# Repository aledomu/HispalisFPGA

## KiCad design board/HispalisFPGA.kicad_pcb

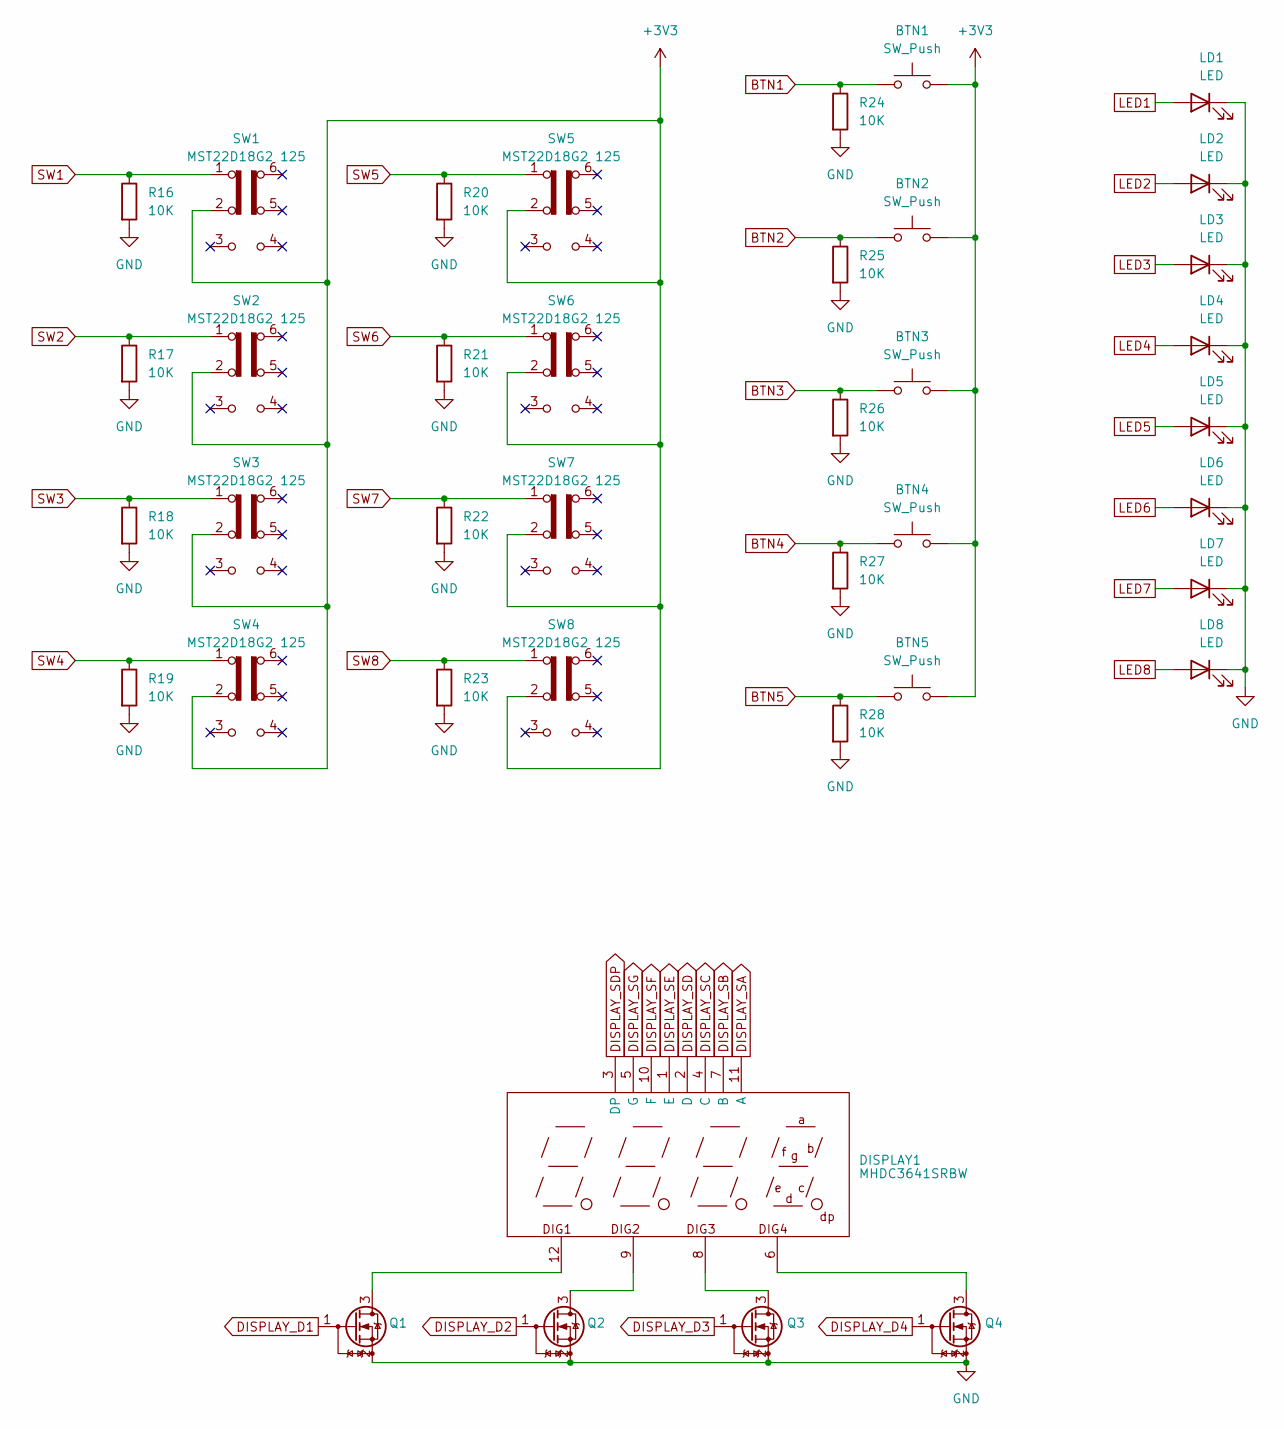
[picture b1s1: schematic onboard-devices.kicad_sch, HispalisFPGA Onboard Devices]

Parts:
BTN1, BTN2, BTN3, BTN4, BTN5: SW_Push; SW_PUSH_6mm; JLC Plugin,6x6mm
DISPLAY1: MHDC3641SRBW; LED-SEG-TH_12P-L30.0-W14.0-P2.54-LS10.2; Manufacturer Part MHDC3641SRBW; LCSC Part Name 0.36共阴四八红色数码管
LD1, LD2, LD3, LD4, LD5, LD6, LD7, LD8: LED; LED_0805_2012Metric; JLC 0805
Q1, Q2, Q3, Q4: DMG1012T; SOT-523; JLC SOT-523
R16, R17, R18, R19, R20, R21, R22, R23, R24, R25, R26, R27, R28: 10K; R_0402_1005Metric; JLC 0402
SW1, SW2, SW3, SW4, SW5, SW6, SW7, SW8: MST22D18G2 125; SW-SMD_MST22D18G2; JLC SMD

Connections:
+3V3: BTN1.2, BTN2.2, BTN3.2, BTN4.2, BTN5.2, SW1.2 (B), SW2.2 (B), SW3.2 (B), SW4.2 (B), SW5.2 (B), SW6.2 (B), SW7.2 (B), SW8.2 (B); also elsewhere on the board
BTN1: BTN1.1, R24.1; also elsewhere on the board
BTN2: BTN2.1, R25.1; also elsewhere on the board
BTN3: BTN3.1, R26.1; also elsewhere on the board
BTN4: BTN4.1, R27.1; also elsewhere on the board
BTN5: BTN5.1, R28.1; also elsewhere on the board
DISPLAY_D1: Q1.1 (G); also elsewhere on the board
DISPLAY_D2: Q2.1 (G); also elsewhere on the board
DISPLAY_D3: Q3.1 (G); also elsewhere on the board
DISPLAY_D4: Q4.1 (G); also elsewhere on the board
DISPLAY_SA: DISPLAY1.11 (A); also elsewhere on the board
DISPLAY_SB: DISPLAY1.7 (B); also elsewhere on the board
DISPLAY_SC: DISPLAY1.4 (C); also elsewhere on the board
DISPLAY_SD: DISPLAY1.2 (D); also elsewhere on the board
DISPLAY_SDP: DISPLAY1.3 (DP); also elsewhere on the board
DISPLAY_SE: DISPLAY1.1 (E); also elsewhere on the board
DISPLAY_SF: DISPLAY1.10 (F); also elsewhere on the board
DISPLAY_SG: DISPLAY1.5 (G); also elsewhere on the board
GND: LD1.1 (K), LD2.1 (K), LD3.1 (K), LD4.1 (K), LD5.1 (K), LD6.1 (K), LD7.1 (K), LD8.1 (K), Q1.2 (S), Q2.2 (S), Q3.2 (S), Q4.2 (S), R16.2, R17.2, R18.2, R19.2, R20.2, R21.2, R22.2, R23.2, R24.2, R25.2, R26.2, R27.2, R28.2; also elsewhere on the board
LED1: LD1.2 (A); also elsewhere on the board
LED2: LD2.2 (A); also elsewhere on the board
LED3: LD3.2 (A); also elsewhere on the board
LED4: LD4.2 (A); also elsewhere on the board
LED5: LD5.2 (A); also elsewhere on the board
LED6: LD6.2 (A); also elsewhere on the board
LED7: LD7.2 (A); also elsewhere on the board
LED8: LD8.2 (A); also elsewhere on the board
unnamed: DISPLAY1.12 (DIG1), Q1.3 (D)
unnamed: DISPLAY1.9 (DIG2), Q2.3 (D)
unnamed: DISPLAY1.8 (DIG3), Q3.3 (D)
unnamed: DISPLAY1.6 (DIG4), Q4.3 (D)
SW1: R16.1, SW1.1 (A); also elsewhere on the board
SW2: R17.1, SW2.1 (A); also elsewhere on the board
SW3: R18.1, SW3.1 (A); also elsewhere on the board
SW4: R19.1, SW4.1 (A); also elsewhere on the board
SW5: R20.1, SW5.1 (A); also elsewhere on the board
SW6: R21.1, SW6.1 (A); also elsewhere on the board
SW7: R22.1, SW7.1 (A); also elsewhere on the board
SW8: R23.1, SW8.1 (A); also elsewhere on the board

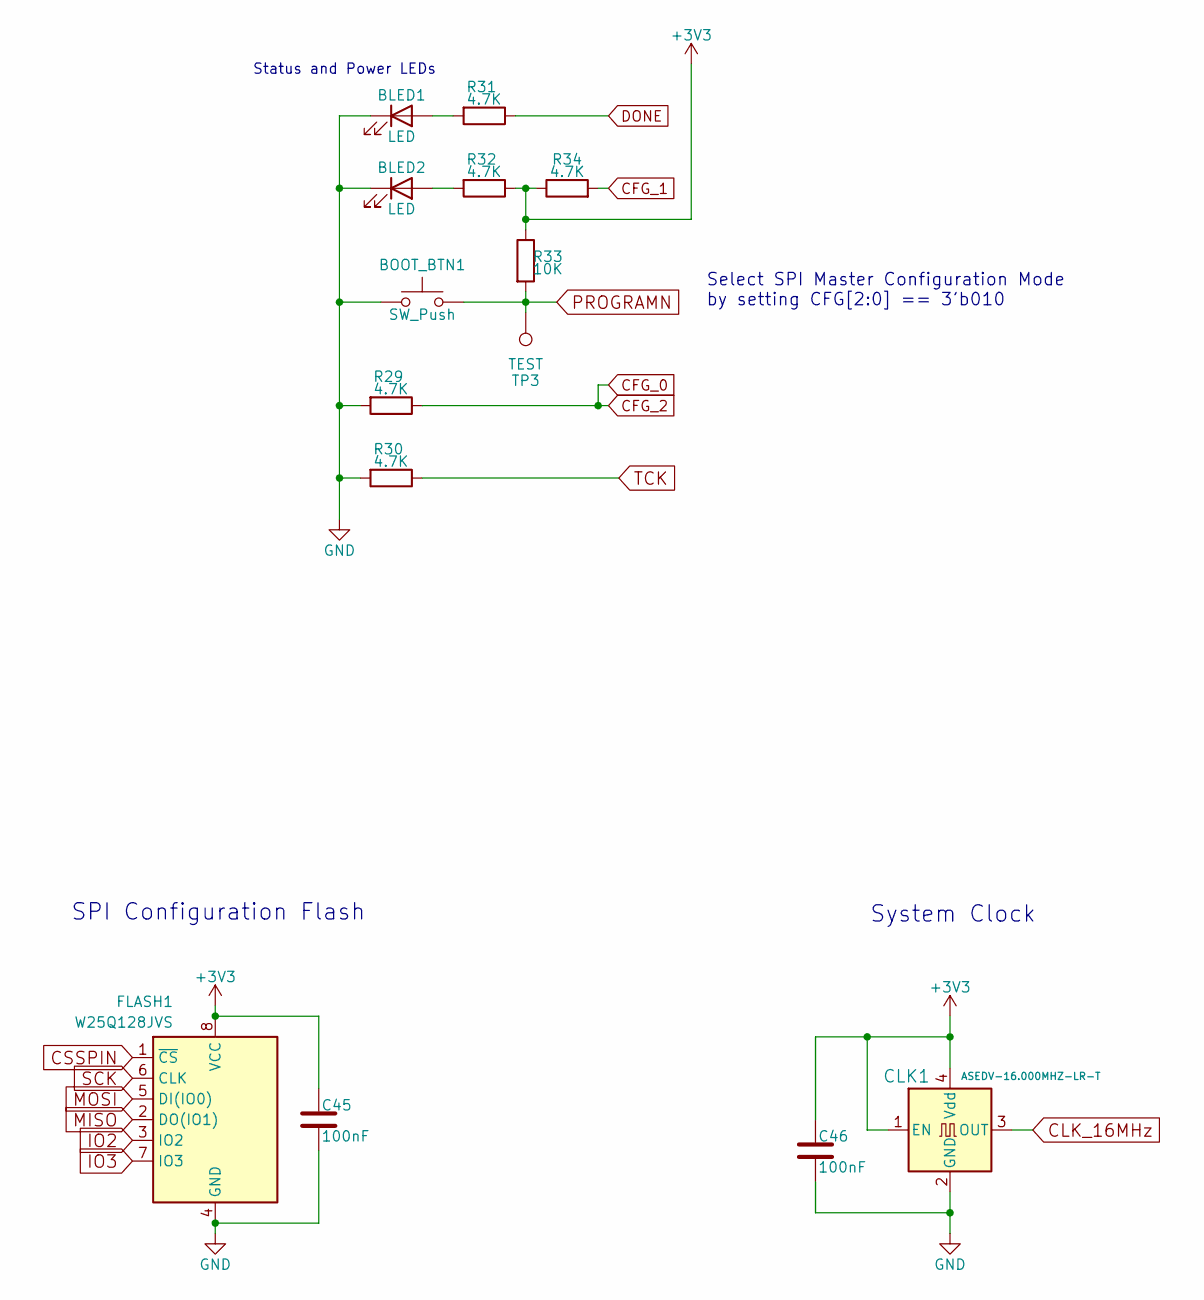
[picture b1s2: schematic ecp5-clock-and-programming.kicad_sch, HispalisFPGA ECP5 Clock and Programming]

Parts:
BLED1, BLED2: LED; LED_0603_1608Metric; JLC 0603
BOOT_BTN1: SW_Push; SW_PUSH_6mm; JLC Plugin,6x6mm
C45, C46: 100nF; C_0402_1005Metric; JLC 0402
CLK1: ASEDV-16.000MHZ-LR-T; Oscillator_SMD_Abracon_ASE-4Pin_3.2x2.5mm; JLC SMD3225-4P
FLASH1: W25Q128JVS; SOIC-8_5.23x5.23mm_P1.27mm; JLC SOIC-8-208mil
R29, R30, R31, R32, R34: 4.7K; R_0402_1005Metric; JLC 0402
R33: 10K; R_0402_1005Metric; JLC 0402
TP3: TEST; TestPoint_Pad_D1.0mm

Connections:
+3V3: C45.1, C46.1, CLK1.1 (EN), CLK1.4 (Vdd), FLASH1.8 (VCC), R32.1, R33.1, R34.1; also elsewhere on the board
CFG_0: R29.1; also elsewhere on the board
CFG_1: R34.2; also elsewhere on the board
CLK_16MHz: CLK1.3 (OUT); also elsewhere on the board
CSSPIN: FLASH1.1 (~CS); also elsewhere on the board
DONE: R31.1; also elsewhere on the board
GND: BLED1.1 (K), BLED2.1 (K), BOOT_BTN1.1, C45.2, C46.2, CLK1.2 (GND), FLASH1.4 (GND), R29.2, R30.2; also elsewhere on the board
IO2: FLASH1.3 (IO2); also elsewhere on the board
IO3: FLASH1.7 (IO3); also elsewhere on the board
MISO: FLASH1.2 (DO(IO1)); also elsewhere on the board
MOSI: FLASH1.5 (DI(IO0)); also elsewhere on the board
unnamed: BLED1.2 (A), R31.2
unnamed: BLED2.2 (A), R32.2
PROGRAMN: BOOT_BTN1.2, R33.2, TP3.1; also elsewhere on the board
SCK: FLASH1.6 (CLK); also elsewhere on the board
TCK: R30.1; also elsewhere on the board

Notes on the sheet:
System Clock
Status and Power LEDs
Select SPI Master Configuration Mode by setting CFG[2:0] == 3'b010
SPI Configuration Flash

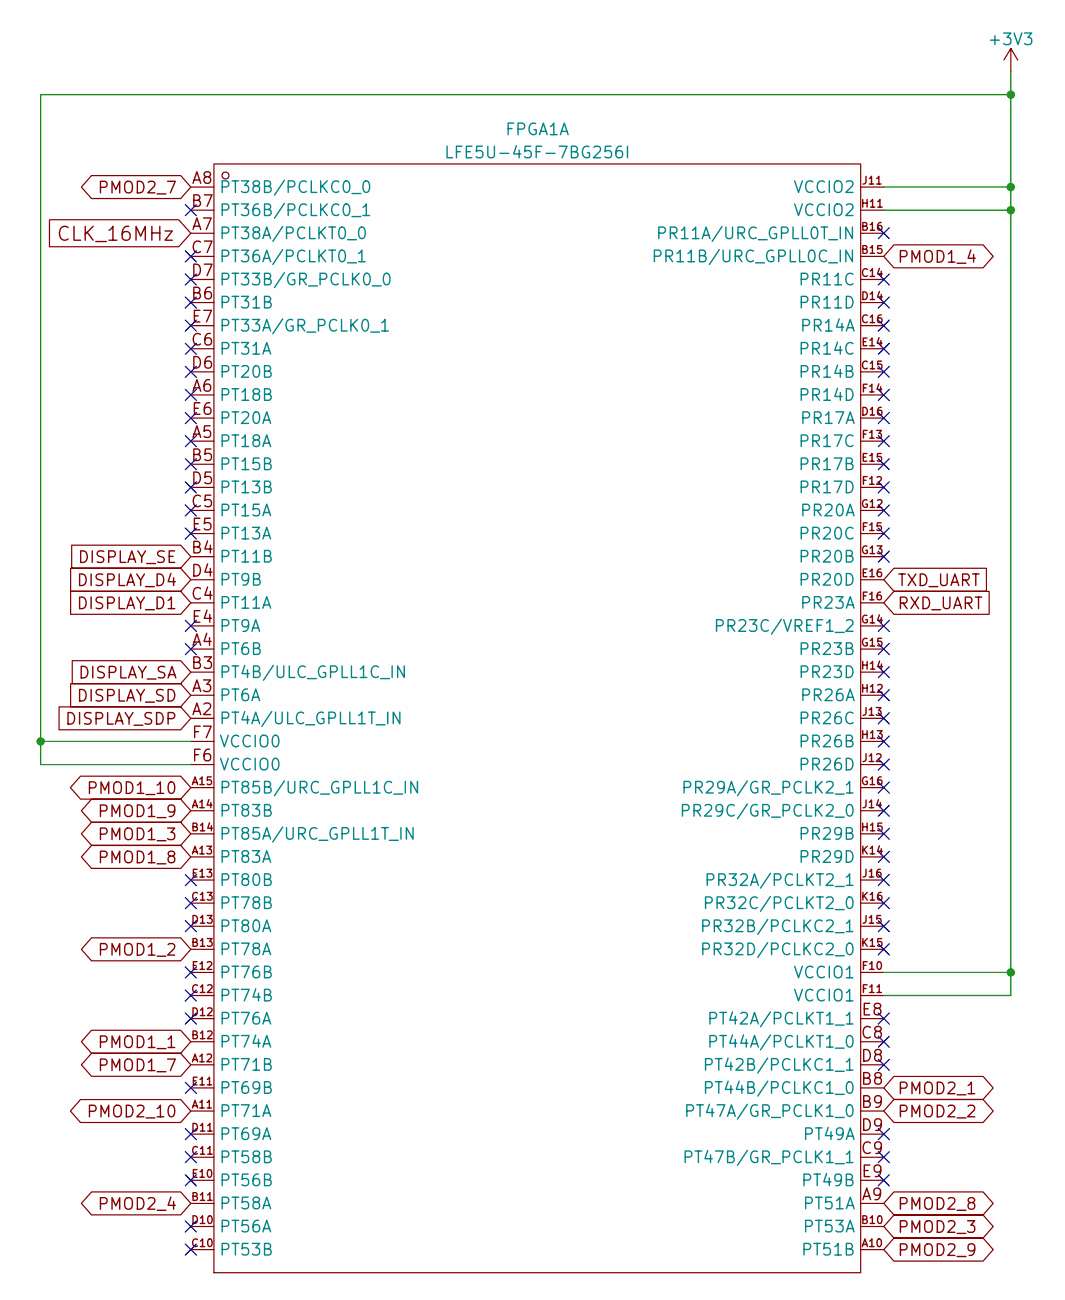
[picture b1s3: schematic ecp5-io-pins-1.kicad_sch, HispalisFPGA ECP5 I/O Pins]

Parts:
FPGA1: LFE5U-45F-7BG256I; CABGA-256_L14.0-W14.0-R16-C16-P0.80-TL; Manufacturer Part LFE5U-45F-7BG256I; LCSC Part Name LFE5U 45F 7BG256I

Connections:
+3V3: FPGA1.F6 (VCCIO0), FPGA1.F7 (VCCIO0), FPGA1.F10 (VCCIO1), FPGA1.F11 (VCCIO1), FPGA1.H11 (VCCIO2), FPGA1.J11 (VCCIO2); also elsewhere on the board
CLK_16MHz: FPGA1.A7 (PT38A/PCLKT0_0); also elsewhere on the board
DISPLAY_D1: FPGA1.C4 (PT11A); also elsewhere on the board
DISPLAY_D4: FPGA1.D4 (PT9B); also elsewhere on the board
DISPLAY_SA: FPGA1.B3 (PT4B/ULC_GPLL1C_IN); also elsewhere on the board
DISPLAY_SD: FPGA1.A3 (PT6A); also elsewhere on the board
DISPLAY_SDP: FPGA1.A2 (PT4A/ULC_GPLL1T_IN); also elsewhere on the board
DISPLAY_SE: FPGA1.B4 (PT11B); also elsewhere on the board
PMOD1_1: FPGA1.B12 (PT74A); also elsewhere on the board
PMOD1_2: FPGA1.B13 (PT78A); also elsewhere on the board
PMOD1_3: FPGA1.B14 (PT85A/URC_GPLL1T_IN); also elsewhere on the board
PMOD1_4: FPGA1.B15 (PR11B/URC_GPLL0C_IN); also elsewhere on the board
PMOD1_7: FPGA1.A12 (PT71B); also elsewhere on the board
PMOD1_8: FPGA1.A13 (PT83A); also elsewhere on the board
PMOD1_9: FPGA1.A14 (PT83B); also elsewhere on the board
PMOD1_10: FPGA1.A15 (PT85B/URC_GPLL1C_IN); also elsewhere on the board
PMOD2_1: FPGA1.B8 (PT44B/PCLKC1_0); also elsewhere on the board
PMOD2_2: FPGA1.B9 (PT47A/GR_PCLK1_0); also elsewhere on the board
PMOD2_3: FPGA1.B10 (PT53A); also elsewhere on the board
PMOD2_4: FPGA1.B11 (PT58A); also elsewhere on the board
PMOD2_7: FPGA1.A8 (PT38B/PCLKC0_0); also elsewhere on the board
PMOD2_8: FPGA1.A9 (PT51A); also elsewhere on the board
PMOD2_9: FPGA1.A10 (PT51B); also elsewhere on the board
PMOD2_10: FPGA1.A11 (PT71A); also elsewhere on the board
RXD_UART: FPGA1.F16 (PR23A); also elsewhere on the board
TXD_UART: FPGA1.E16 (PR20D); also elsewhere on the board

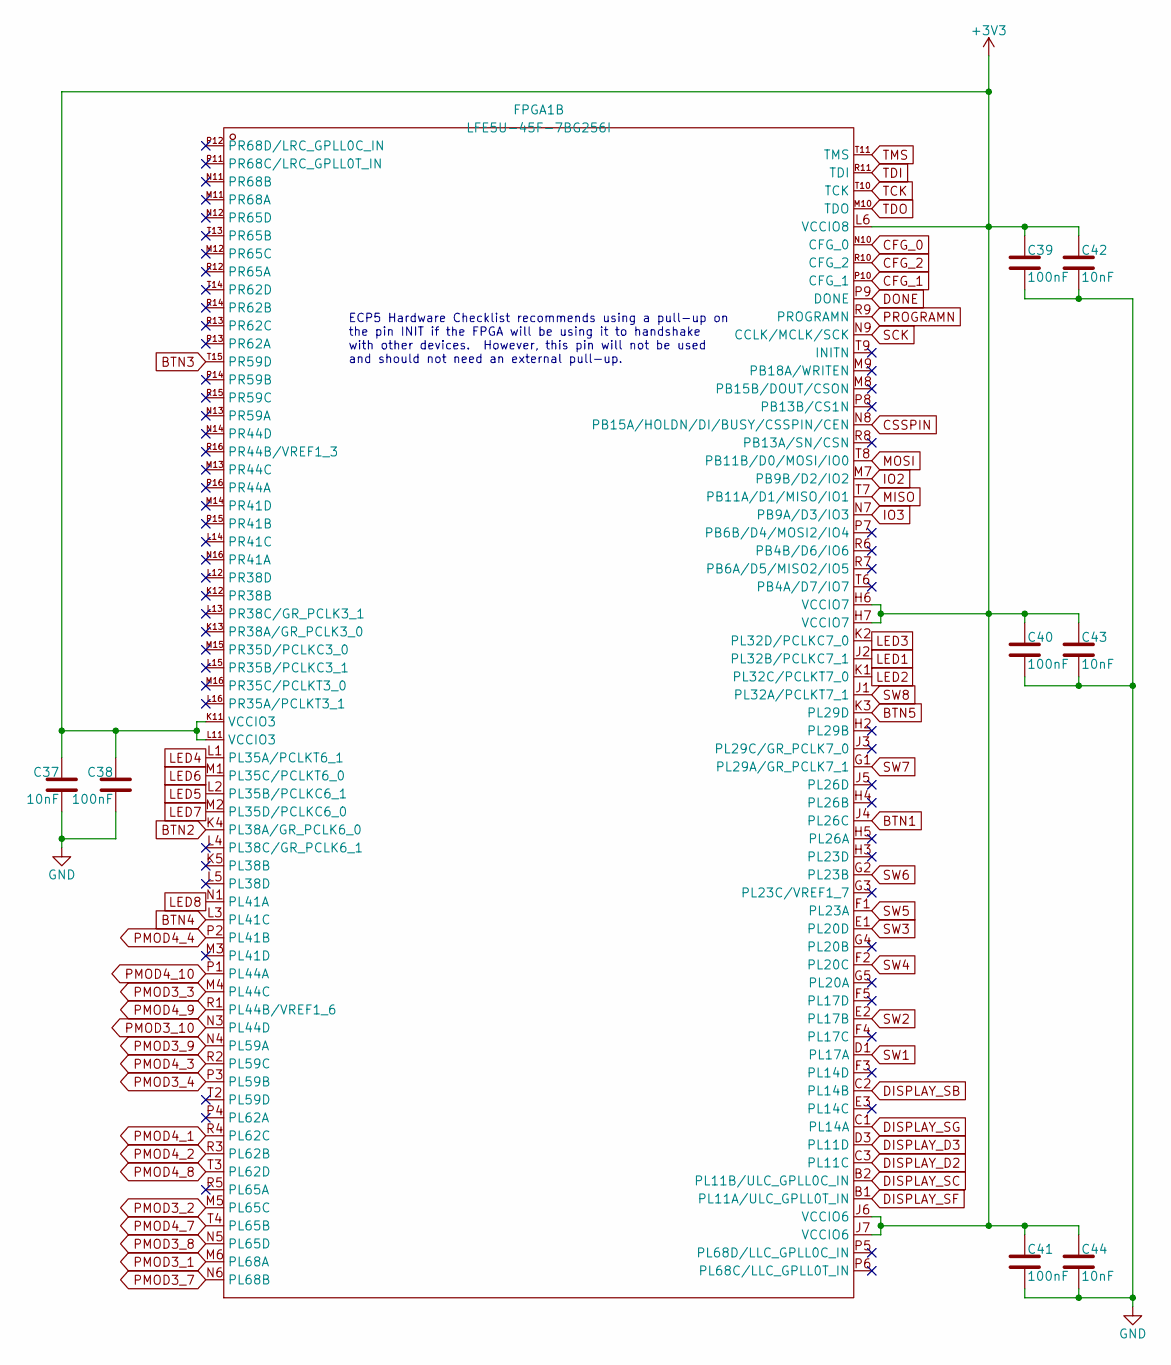
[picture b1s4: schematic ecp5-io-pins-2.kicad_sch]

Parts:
C37, C42, C43, C44: 10nF; C_0402_1005Metric; JLC 0402
C38, C39, C40, C41: 100nF; C_0402_1005Metric; JLC 0402
FPGA1: LFE5U-45F-7BG256I; CABGA-256_L14.0-W14.0-R16-C16-P0.80-TL; Manufacturer Part LFE5U-45F-7BG256I; LCSC Part Name LFE5U 45F 7BG256I

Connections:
+3V3: C37.1, C38.1, C39.1, C40.1, C41.1, C42.1, C43.1, C44.1, FPGA1.H6 (VCCIO7), FPGA1.H7 (VCCIO7), FPGA1.J6 (VCCIO6), FPGA1.J7 (VCCIO6), FPGA1.K11 (VCCIO3), FPGA1.L6 (VCCIO8), FPGA1.L11 (VCCIO3); also elsewhere on the board
BTN1: FPGA1.J4 (PL26C); also elsewhere on the board
BTN2: FPGA1.K4 (PL38A/GR_PCLK6_0); also elsewhere on the board
BTN3: FPGA1.T15 (PR59D); also elsewhere on the board
BTN4: FPGA1.L3 (PL41C); also elsewhere on the board
BTN5: FPGA1.K3 (PL29D); also elsewhere on the board
CFG_0: FPGA1.N10 (CFG_0), FPGA1.R10 (CFG_2); also elsewhere on the board
CFG_1: FPGA1.P10 (CFG_1); also elsewhere on the board
CSSPIN: FPGA1.N8 (PB15A/HOLDN/DI/BUSY/CSSPIN/CEN); also elsewhere on the board
DISPLAY_D2: FPGA1.C3 (PL11C); also elsewhere on the board
DISPLAY_D3: FPGA1.D3 (PL11D); also elsewhere on the board
DISPLAY_SB: FPGA1.C2 (PL14B); also elsewhere on the board
DISPLAY_SC: FPGA1.B2 (PL11B/ULC_GPLL0C_IN); also elsewhere on the board
DISPLAY_SF: FPGA1.B1 (PL11A/ULC_GPLL0T_IN); also elsewhere on the board
DISPLAY_SG: FPGA1.C1 (PL14A); also elsewhere on the board
DONE: FPGA1.P9 (DONE); also elsewhere on the board
GND: C37.2, C38.2, C39.2, C40.2, C41.2, C42.2, C43.2, C44.2; also elsewhere on the board
IO2: FPGA1.M7 (PB9B/D2/IO2); also elsewhere on the board
IO3: FPGA1.N7 (PB9A/D3/IO3); also elsewhere on the board
LED1: FPGA1.J2 (PL32B/PCLKC7_1); also elsewhere on the board
LED2: FPGA1.K1 (PL32C/PCLKT7_0); also elsewhere on the board
LED3: FPGA1.K2 (PL32D/PCLKC7_0); also elsewhere on the board
LED4: FPGA1.L1 (PL35A/PCLKT6_1); also elsewhere on the board
LED5: FPGA1.L2 (PL35B/PCLKC6_1); also elsewhere on the board
LED6: FPGA1.M1 (PL35C/PCLKT6_0); also elsewhere on the board
LED7: FPGA1.M2 (PL35D/PCLKC6_0); also elsewhere on the board
LED8: FPGA1.N1 (PL41A); also elsewhere on the board
MISO: FPGA1.T7 (PB11A/D1/MISO/IO1); also elsewhere on the board
MOSI: FPGA1.T8 (PB11B/D0/MOSI/IO0); also elsewhere on the board
PMOD3_1: FPGA1.M6 (PL68A); also elsewhere on the board
PMOD3_2: FPGA1.M5 (PL65C); also elsewhere on the board
PMOD3_3: FPGA1.M4 (PL44C); also elsewhere on the board
PMOD3_4: FPGA1.P3 (PL59B); also elsewhere on the board
PMOD3_7: FPGA1.N6 (PL68B); also elsewhere on the board
PMOD3_8: FPGA1.N5 (PL65D); also elsewhere on the board
PMOD3_9: FPGA1.N4 (PL59A); also elsewhere on the board
PMOD3_10: FPGA1.N3 (PL44D); also elsewhere on the board
PMOD4_1: FPGA1.R4 (PL62C); also elsewhere on the board
PMOD4_2: FPGA1.R3 (PL62B); also elsewhere on the board
PMOD4_3: FPGA1.R2 (PL59C); also elsewhere on the board
PMOD4_4: FPGA1.P2 (PL41B); also elsewhere on the board
PMOD4_7: FPGA1.T4 (PL65B); also elsewhere on the board
PMOD4_8: FPGA1.T3 (PL62D); also elsewhere on the board
PMOD4_9: FPGA1.R1 (PL44B/VREF1_6); also elsewhere on the board
PMOD4_10: FPGA1.P1 (PL44A); also elsewhere on the board
PROGRAMN: FPGA1.R9 (PROGRAMN); also elsewhere on the board
SCK: FPGA1.N9 (CCLK/MCLK/SCK); also elsewhere on the board
SW1: FPGA1.D1 (PL17A); also elsewhere on the board
SW2: FPGA1.E2 (PL17B); also elsewhere on the board
SW3: FPGA1.E1 (PL20D); also elsewhere on the board
SW4: FPGA1.F2 (PL20C); also elsewhere on the board
SW5: FPGA1.F1 (PL23A); also elsewhere on the board
SW6: FPGA1.G2 (PL23B); also elsewhere on the board
SW7: FPGA1.G1 (PL29A/GR_PCLK7_1); also elsewhere on the board
SW8: FPGA1.J1 (PL32A/PCLKT7_1); also elsewhere on the board
TCK: FPGA1.T10 (TCK); also elsewhere on the board
TDI: FPGA1.R11 (TDI); also elsewhere on the board
TDO: FPGA1.M10 (TDO); also elsewhere on the board
TMS: FPGA1.T11 (TMS); also elsewhere on the board

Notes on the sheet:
ECP5 Hardware Checklist recommends using a pull-up on the pin INIT if the FPGA will be using it to handshake with other devices. However, this pin will not be used and should not need an external pull-up.

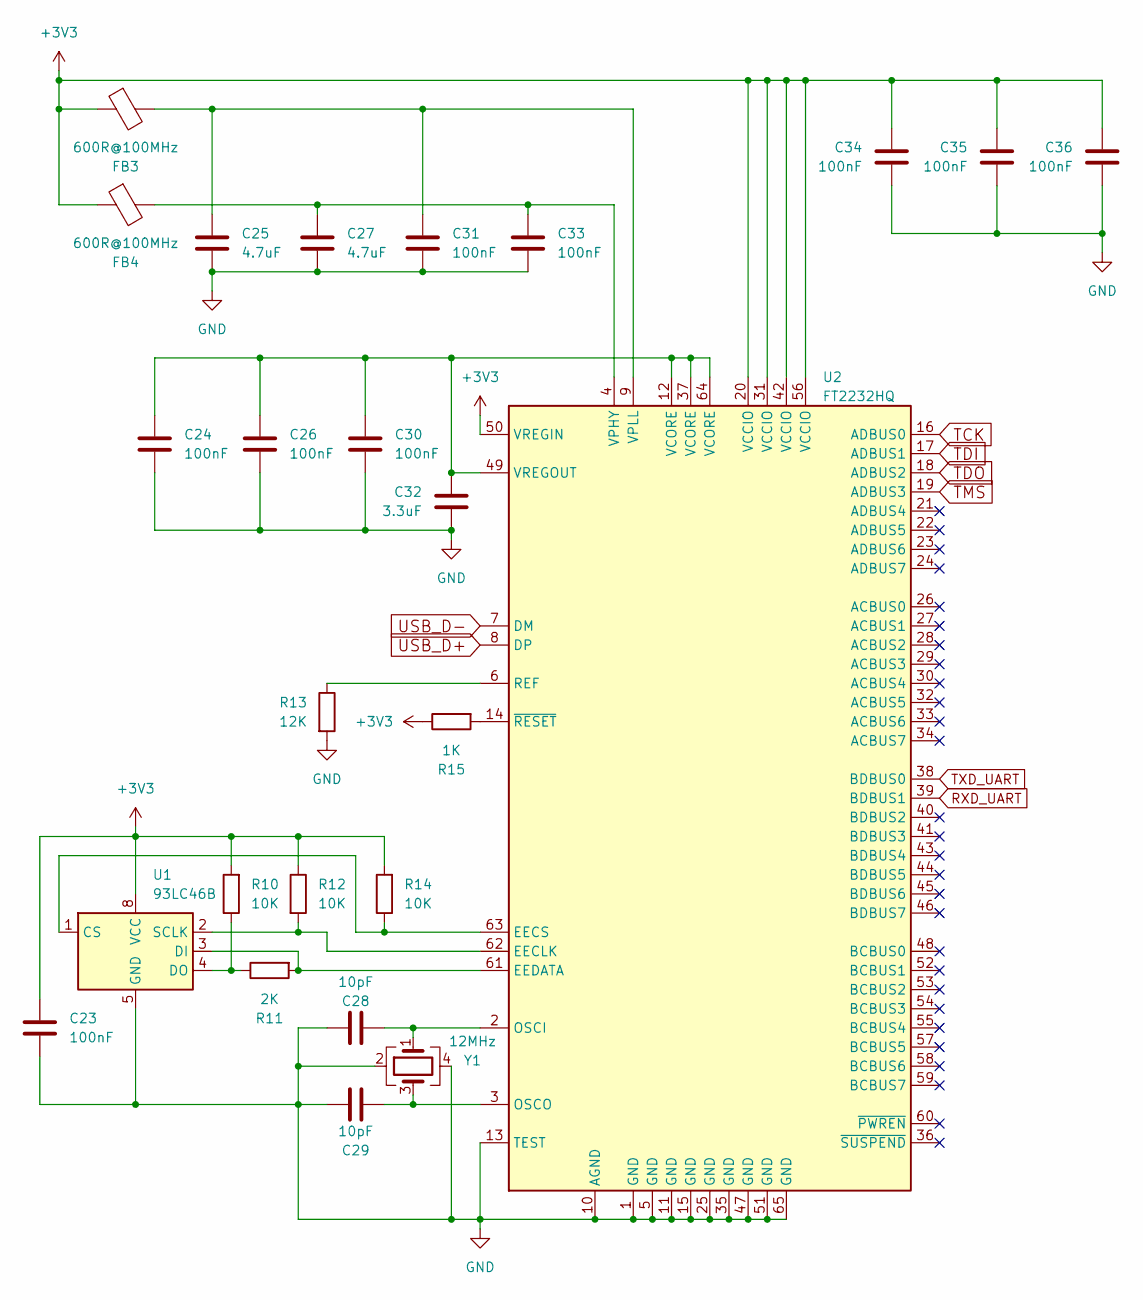
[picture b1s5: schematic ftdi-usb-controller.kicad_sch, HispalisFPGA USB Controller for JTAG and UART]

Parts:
C23, C24, C26, C30, C31, C33, C34, C35, C36: 100nF; C_0402_1005Metric; JLC 0402
C25, C27: 4.7uF; C_0402_1005Metric; JLC 0402
C28, C29: 10pF; C_0402_1005Metric; JLC 0402
C32: 3.3uF; C_0402_1005Metric; JLC 0402
FB3, FB4: 600R@100MHz; L_0603_1608Metric; JLC 0603
R10, R12, R14: 10K; R_0402_1005Metric; JLC 0402
R11: 2K; R_0402_1005Metric; JLC 0402
R13: 12K; R_0402_1005Metric; JLC 0402
R15: 1K; R_0402_1005Metric; JLC 0402
U1: 93LC46B; TSSOP-8_4.4x3mm_P0.65mm; JLC TSSOP-8
U2: FT2232HQ; QFN-64-1EP_9x9mm_P0.5mm_EP4.35x4.35mm; JLC QFN-64-EP(9x9)
Y1: 12MHz; Crystal_SMD_2520-4Pin_2.5x2.0mm; JLC SMD2520-4P

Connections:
+3V3: C23.1, C34.1, C35.1, C36.1, FB3.1, FB4.1, R10.2, R12.1, R14.2, R15.1, U1.8 (VCC), U2.20 (VCCIO), U2.31 (VCCIO), U2.42 (VCCIO), U2.50 (VREGIN), U2.56 (VCCIO); also elsewhere on the board
GND: C23.2, C24.2, C25.2, C26.2, C27.2, C28.1, C29.1, C30.2, C31.2, C32.2, C33.2, C34.2, C35.2, C36.2, R13.2, U1.5 (GND), U2.1 (GND), U2.5 (GND), U2.10 (AGND), U2.11 (GND), U2.13 (TEST), U2.15 (GND), U2.25 (GND), U2.35 (GND), U2.47 (GND), U2.51 (GND), U2.65 (GND), Y1.2, Y1.4; also elsewhere on the board
unnamed: R14.1, U1.1 (CS), U2.63 (EECS)
unnamed: R11.2, U1.3 (DI), U2.61 (EEDATA)
unnamed: R10.1, R11.1, U1.4 (DO)
unnamed: R12.2, U1.2 (SCLK), U2.62 (EECLK)
unnamed: C28.2, U2.2 (OSCI), Y1.1
unnamed: C29.2, U2.3 (OSCO), Y1.3
unnamed: R13.1, U2.6 (REF)
unnamed: C27.1, C33.1, FB4.2, U2.4 (VPHY)
unnamed: C25.1, C31.1, FB3.2, U2.9 (VPLL)
unnamed: C24.1, C26.1, C30.1, C32.1, U2.12 (VCORE), U2.37 (VCORE), U2.49 (VREGOUT), U2.64 (VCORE)
unnamed: R15.2, U2.14 (~RESET)
RXD_UART: U2.39 (BDBUS1); also elsewhere on the board
TCK: U2.16 (ADBUS0); also elsewhere on the board
TDI: U2.17 (ADBUS1); also elsewhere on the board
TDO: U2.18 (ADBUS2); also elsewhere on the board
TMS: U2.19 (ADBUS3); also elsewhere on the board
TXD_UART: U2.38 (BDBUS0); also elsewhere on the board
USB_D+: U2.8 (DP); also elsewhere on the board
USB_D-: U2.7 (DM); also elsewhere on the board

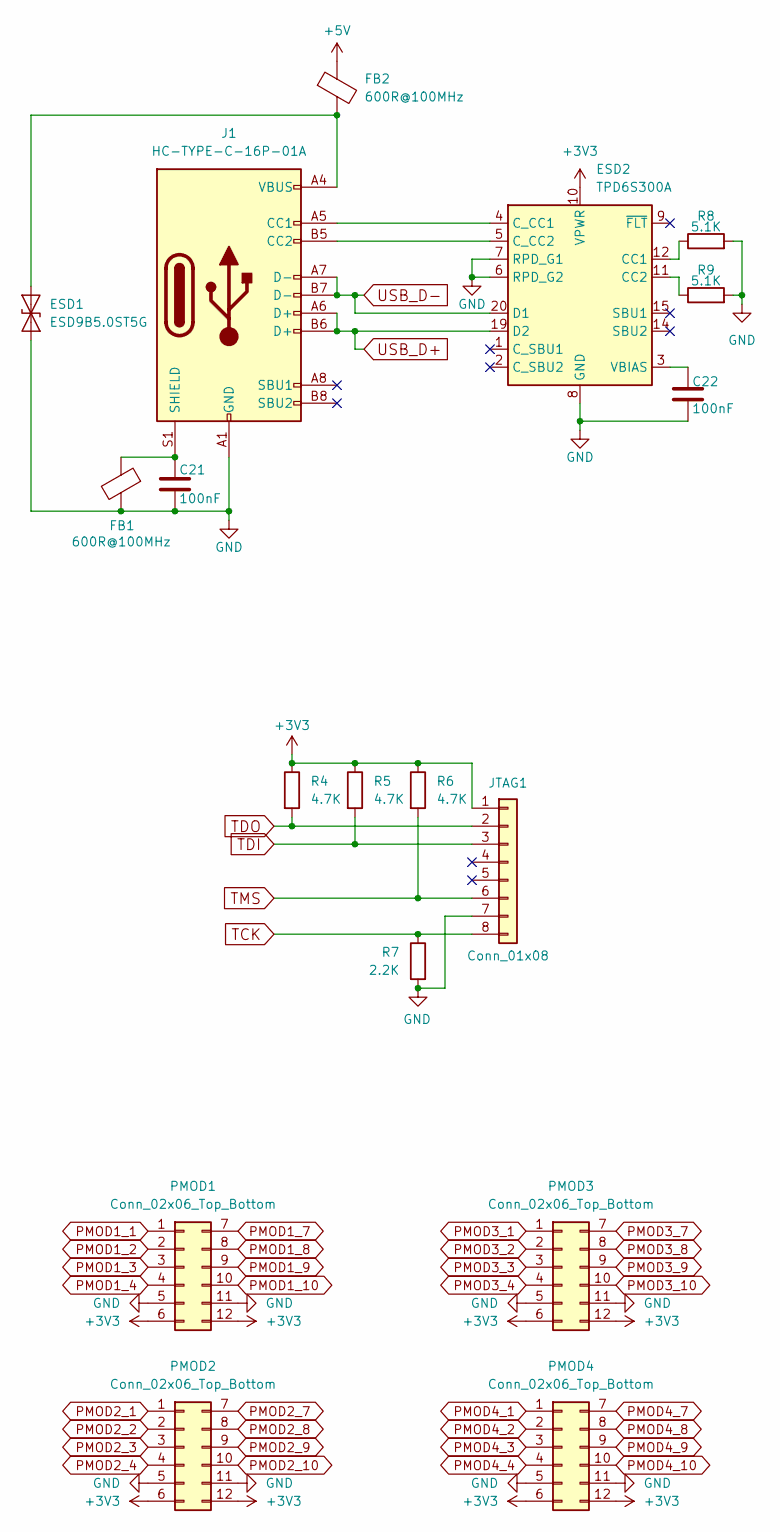
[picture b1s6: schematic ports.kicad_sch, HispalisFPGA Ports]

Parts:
C21, C22: 100nF; C_0402_1005Metric; JLC 0402
ESD1: ESD9B5.0ST5G; D_SOD-923; JLC SOD-923
ESD2: TPD6S300A; WQFN-20-1EP_3x3mm_P0.4mm_EP1.7x1.7mm_ThermalVias; JLC WQFN-20-EP(3x3)
FB1, FB2: 600R@100MHz; L_0603_1608Metric; JLC 0603
J1: HC-TYPE-C-16P-01A; USB_C_Receptacle_HCTL_HC-TYPE-C-16P-01A; JLC SMD
JTAG1: Conn_01x08; PinHeader_1x08_P2.54mm_Vertical; JLC Plugin,P=2.54mm
PMOD1, PMOD2, PMOD3, PMOD4: Conn_02x06_Top_Bottom; PMOD_Socket_Horizontal; JLC Push-Pull,P=2.5mm
R4, R5, R6: 4.7K; R_0402_1005Metric; JLC 0402
R7: 2.2K; R_0402_1005Metric; JLC 0402
R8, R9: 5.1K; R_0402_1005Metric; JLC 0402

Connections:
+3V3: ESD2.10 (VPWR), JTAG1.1, PMOD1.6, PMOD1.12, PMOD2.6, PMOD2.12, PMOD3.6, PMOD3.12, PMOD4.6, PMOD4.12, R4.1, R5.1, R6.1; also elsewhere on the board
+5V: FB2.1; also elsewhere on the board
GND: C21.2, C22.2, ESD1.1 (A1), ESD2.6 (RPD_G2), ESD2.7 (RPD_G1), ESD2.8 (GND), ESD2.13 (GND), ESD2.16 (GND), ESD2.17 (GND), ESD2.18 (GND), ESD2.21 (GND), FB1.2, J1.A1 (GND), J1.A12 (GND), J1.B1 (GND), J1.B12 (GND), JTAG1.7, PMOD1.5, PMOD1.11, PMOD2.5, PMOD2.11, PMOD3.5, PMOD3.11, PMOD4.5, PMOD4.11, R7.2, R8.2, R9.2; also elsewhere on the board
unnamed: ESD1.2 (A2), FB2.2, J1.A4 (VBUS), J1.A9 (VBUS), J1.B4 (VBUS), J1.B9 (VBUS)
unnamed: ESD2.12 (CC1), R8.1
unnamed: ESD2.11 (CC2), R9.1
unnamed: ESD2.4 (C_CC1), J1.A5 (CC1)
unnamed: ESD2.5 (C_CC2), J1.B5 (CC2)
unnamed: C22.1, ESD2.3 (VBIAS)
unnamed: C21.1, FB1.1, J1.S1 (SHIELD)
PMOD1_1: PMOD1.1; also elsewhere on the board
PMOD1_2: PMOD1.2; also elsewhere on the board
PMOD1_3: PMOD1.3; also elsewhere on the board
PMOD1_4: PMOD1.4; also elsewhere on the board
PMOD1_7: PMOD1.7; also elsewhere on the board
PMOD1_8: PMOD1.8; also elsewhere on the board
PMOD1_9: PMOD1.9; also elsewhere on the board
PMOD1_10: PMOD1.10; also elsewhere on the board
PMOD2_1: PMOD2.1; also elsewhere on the board
PMOD2_2: PMOD2.2; also elsewhere on the board
PMOD2_3: PMOD2.3; also elsewhere on the board
PMOD2_4: PMOD2.4; also elsewhere on the board
PMOD2_7: PMOD2.7; also elsewhere on the board
PMOD2_8: PMOD2.8; also elsewhere on the board
PMOD2_9: PMOD2.9; also elsewhere on the board
PMOD2_10: PMOD2.10; also elsewhere on the board
PMOD3_1: PMOD3.1; also elsewhere on the board
PMOD3_2: PMOD3.2; also elsewhere on the board
PMOD3_3: PMOD3.3; also elsewhere on the board
PMOD3_4: PMOD3.4; also elsewhere on the board
PMOD3_7: PMOD3.7; also elsewhere on the board
PMOD3_8: PMOD3.8; also elsewhere on the board
PMOD3_9: PMOD3.9; also elsewhere on the board
PMOD3_10: PMOD3.10; also elsewhere on the board
PMOD4_1: PMOD4.1; also elsewhere on the board
PMOD4_2: PMOD4.2; also elsewhere on the board
PMOD4_3: PMOD4.3; also elsewhere on the board
PMOD4_4: PMOD4.4; also elsewhere on the board
PMOD4_7: PMOD4.7; also elsewhere on the board
PMOD4_8: PMOD4.8; also elsewhere on the board
PMOD4_9: PMOD4.9; also elsewhere on the board
PMOD4_10: PMOD4.10; also elsewhere on the board
TCK: JTAG1.8, R7.1; also elsewhere on the board
TDI: JTAG1.3, R5.2; also elsewhere on the board
TDO: JTAG1.2, R4.2; also elsewhere on the board
TMS: JTAG1.6, R6.2; also elsewhere on the board
USB_D+: ESD2.19 (D2), J1.A6 (D+), J1.B6 (D+); also elsewhere on the board
USB_D-: ESD2.20 (D1), J1.A7 (D-), J1.B7 (D-); also elsewhere on the board

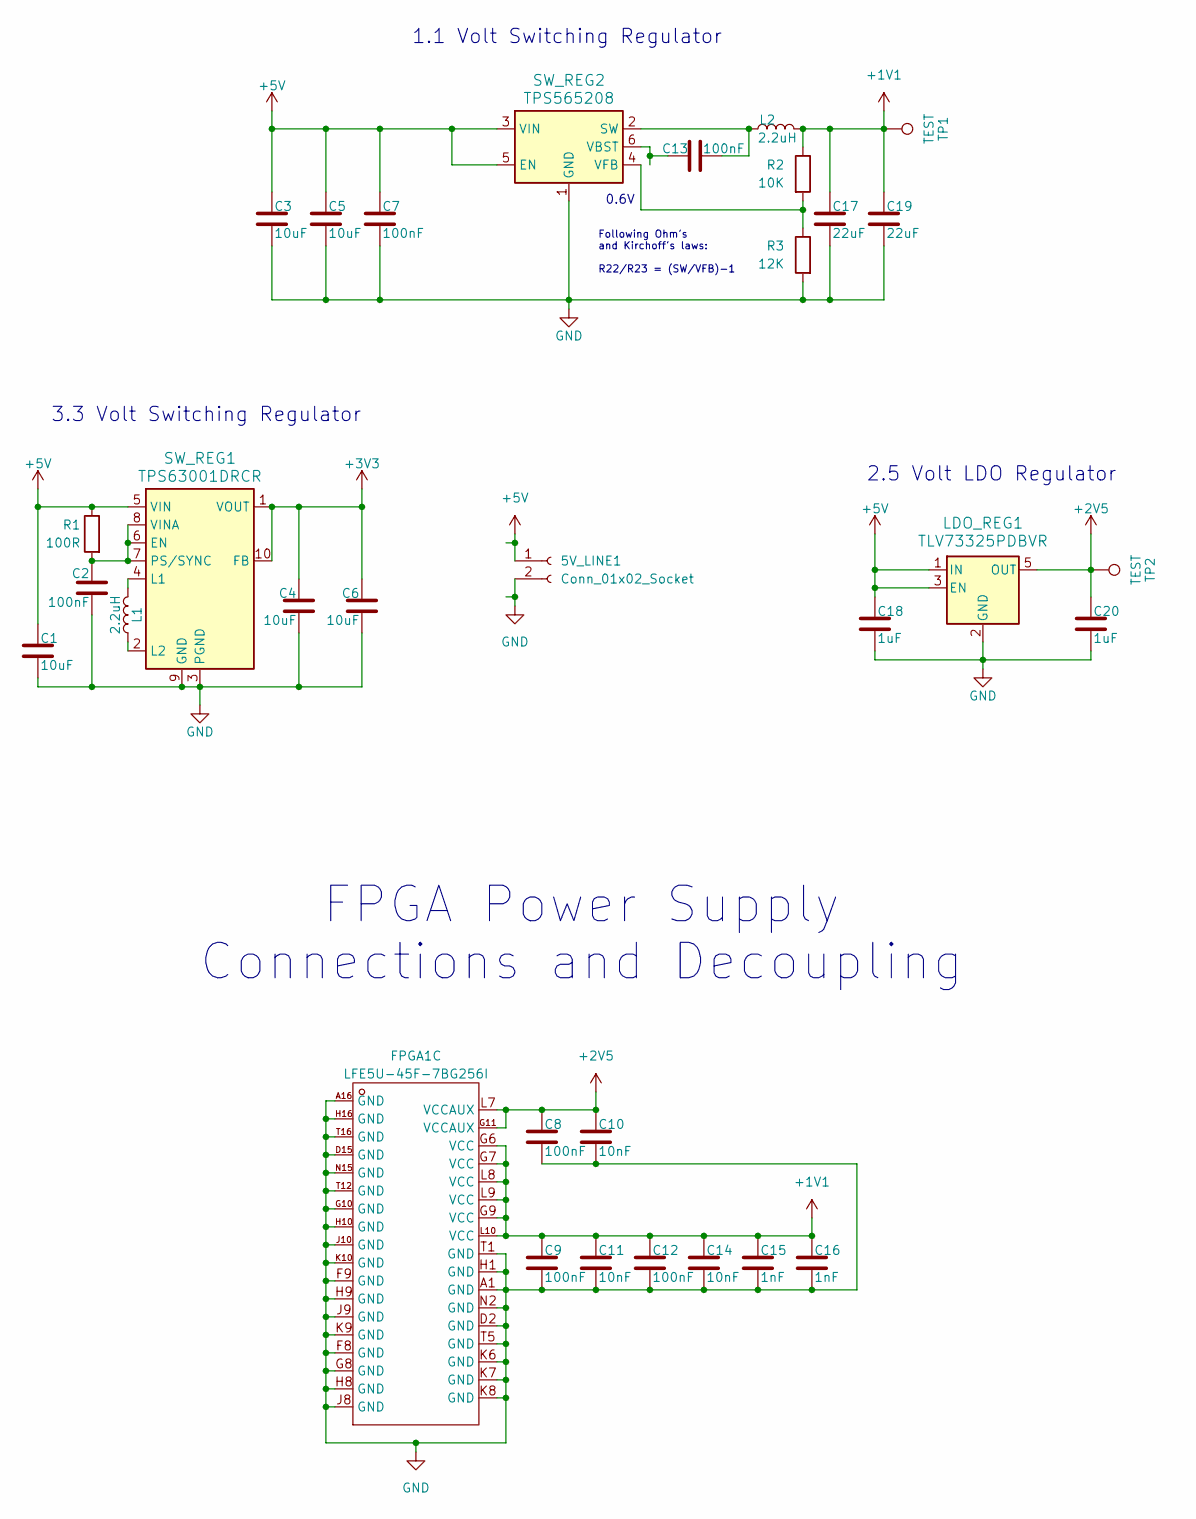
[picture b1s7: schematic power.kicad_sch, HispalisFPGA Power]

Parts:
5V_LINE1: Conn_01x02_Socket; PinSocket_1x02_P2.54mm_Vertical; JLC Plugin,P=2.54mm
C1, C3, C4, C5, C6: 10uF; C_0603_1608Metric; JLC 0603
C2, C7, C8, C9, C12, C13: 100nF; C_0402_1005Metric; JLC 0402
C10, C11, C14: 10nF; C_0402_1005Metric; JLC 0402
C15, C16: 1nF; C_0402_1005Metric; JLC 0402
C17, C19: 22uF; C_0603_1608Metric; JLC 0603
C18, C20: 1uF; C_0402_1005Metric; JLC 0402
FPGA1: LFE5U-45F-7BG256I; CABGA-256_L14.0-W14.0-R16-C16-P0.80-TL; Manufacturer Part LFE5U-45F-7BG256I; LCSC Part Name LFE5U 45F 7BG256I
L1, L2: 2.2uH; L_0805_2012Metric; JLC 0805
LDO_REG1: TLV73325PDBVR; SOT-23-5; JLC SOT-23-5
R1: 100R; R_0402_1005Metric; JLC 0402
R2: 10K; R_0402_1005Metric; JLC 0402
R3: 12K; R_0402_1005Metric; JLC 0402
SW_REG1: TPS63001DRCR; Texas_DRC0010J_ThermalVias; JLC VSON-10-EP(3x3)
SW_REG2: TPS565208; SOT-23-6; JLC TSOT-23-6
TP1, TP2: TEST; TestPoint_Pad_D1.0mm

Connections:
+1V1: C9.1, C11.1, C12.1, C14.1, C15.1, C16.1, C17.1, C19.1, FPGA1.G6 (VCC), FPGA1.G7 (VCC), FPGA1.G9 (VCC), FPGA1.L8 (VCC), FPGA1.L9 (VCC), FPGA1.L10 (VCC), L2.2, R2.1, TP1.1
+2V5: C8.1, C10.1, C20.1, FPGA1.G11 (VCCAUX), FPGA1.L7 (VCCAUX), LDO_REG1.5 (OUT), TP2.1
+3V3: C4.1, C6.1, SW_REG1.1 (VOUT), SW_REG1.10 (FB); also elsewhere on the board
+5V: 5V_LINE1.1, C1.1, C3.1, C5.1, C7.1, C18.1, LDO_REG1.1 (IN), LDO_REG1.3 (EN), R1.1, SW_REG1.5 (VIN), SW_REG2.3 (VIN), SW_REG2.5 (EN); also elsewhere on the board
GND: 5V_LINE1.2, C1.2, C2.1, C3.2, C4.2, C5.2, C6.2, C7.2, C8.2, C9.2, C10.2, C11.2, C12.2, C14.2, C15.2, C16.2, C17.2, C18.2, C19.2, C20.2, FPGA1.A1 (GND), FPGA1.A16 (GND), FPGA1.D2 (GND), FPGA1.D15 (GND), FPGA1.F8 (GND), FPGA1.F9 (GND), FPGA1.G8 (GND), FPGA1.G10 (GND), FPGA1.H1 (GND), FPGA1.H8 (GND), FPGA1.H9 (GND), FPGA1.H10 (GND), FPGA1.H16 (GND), FPGA1.J8 (GND), FPGA1.J9 (GND), FPGA1.J10 (GND), FPGA1.K6 (GND), FPGA1.K7 (GND), FPGA1.K8 (GND), FPGA1.K9 (GND), FPGA1.K10 (GND), FPGA1.N2 (GND), FPGA1.N15 (GND), FPGA1.T1 (GND), FPGA1.T5 (GND), FPGA1.T12 (GND), FPGA1.T16 (GND), LDO_REG1.2 (GND), R3.2, SW_REG1.3 (PGND), SW_REG1.9 (GND), SW_REG1.11 (PGND), SW_REG2.1 (GND); also elsewhere on the board
unnamed: C2.2, R1.2, SW_REG1.6 (EN), SW_REG1.7 (PS/SYNC), SW_REG1.8 (VINA)
unnamed: L1.2, SW_REG1.4 (L1)
unnamed: L1.1, SW_REG1.2 (L2)
unnamed: C13.2, L2.1, SW_REG2.2 (SW)
unnamed: C13.1, SW_REG2.6 (VBST)
unnamed: R2.2, R3.1, SW_REG2.4 (VFB)

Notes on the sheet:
1.1 Volt Switching Regulator
FPGA Power Supply Connections and Decoupling
2.5 Volt LDO Regulator
Following Ohm's and Kirchoff's laws: R22/R23 = (SW/VFB)-1
0.6V
3.3 Volt Switching Regulator
